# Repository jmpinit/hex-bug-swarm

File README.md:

# Hex Bug Swarm

[A blog post explaining what this is for](https://owentrueblood.com/hex-bug-swarm/)

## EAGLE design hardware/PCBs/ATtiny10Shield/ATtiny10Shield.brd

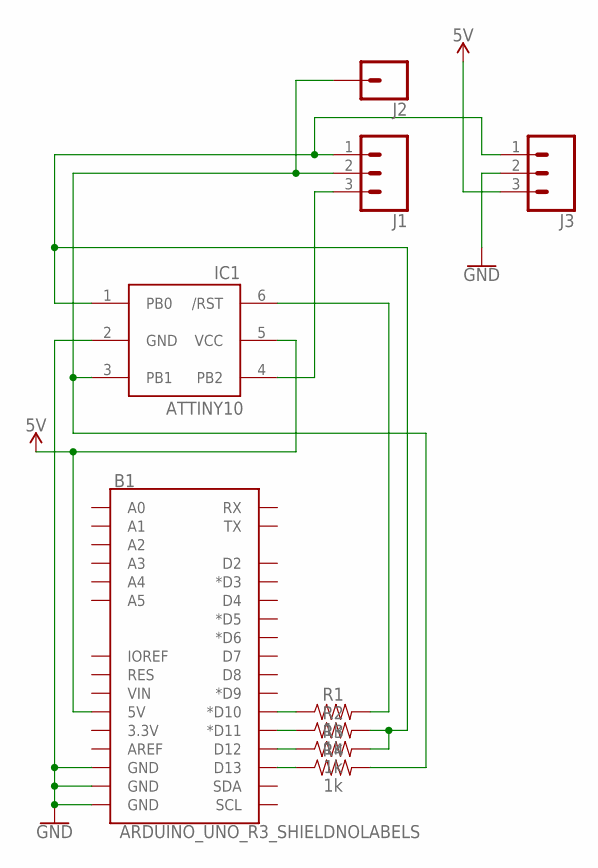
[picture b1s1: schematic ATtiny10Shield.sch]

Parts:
B1: ARDUINO_UNO_R3_SHIELDNOLABELS; UNO_R3_SHIELD_NOLABELS
IC1: ATTINY10; SOT23-6
J1, J3: CONN_03; 1X03
J2: CONN_01; 1X01
R1, R2, R3, R4: 1k; AXIAL-0.3

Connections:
5V: B1.5V, IC1.5 (VCC), J3.3
GND: B1.GND@0 (GND), B1.GND@1 (GND), B1.GND@2 (GND), IC1.2 (GND), J3.2
unnamed: B1.D10 (*D10), R1.P$1 (1)
unnamed: B1.D11 (*D11), R2.P$1 (1)
unnamed: B1.D12, R3.P$1 (1)
unnamed: B1.D13, R4.P$1 (1)
unnamed: IC1.1 (PB0), J1.1, J3.1, R2.P$2 (2), R3.P$2 (2)
unnamed: IC1.6 (/RST), R1.P$2 (2)
unnamed: IC1.3 (PB1), J1.2, J2.1, R4.P$2 (2)
unnamed: IC1.4 (PB2), J1.3

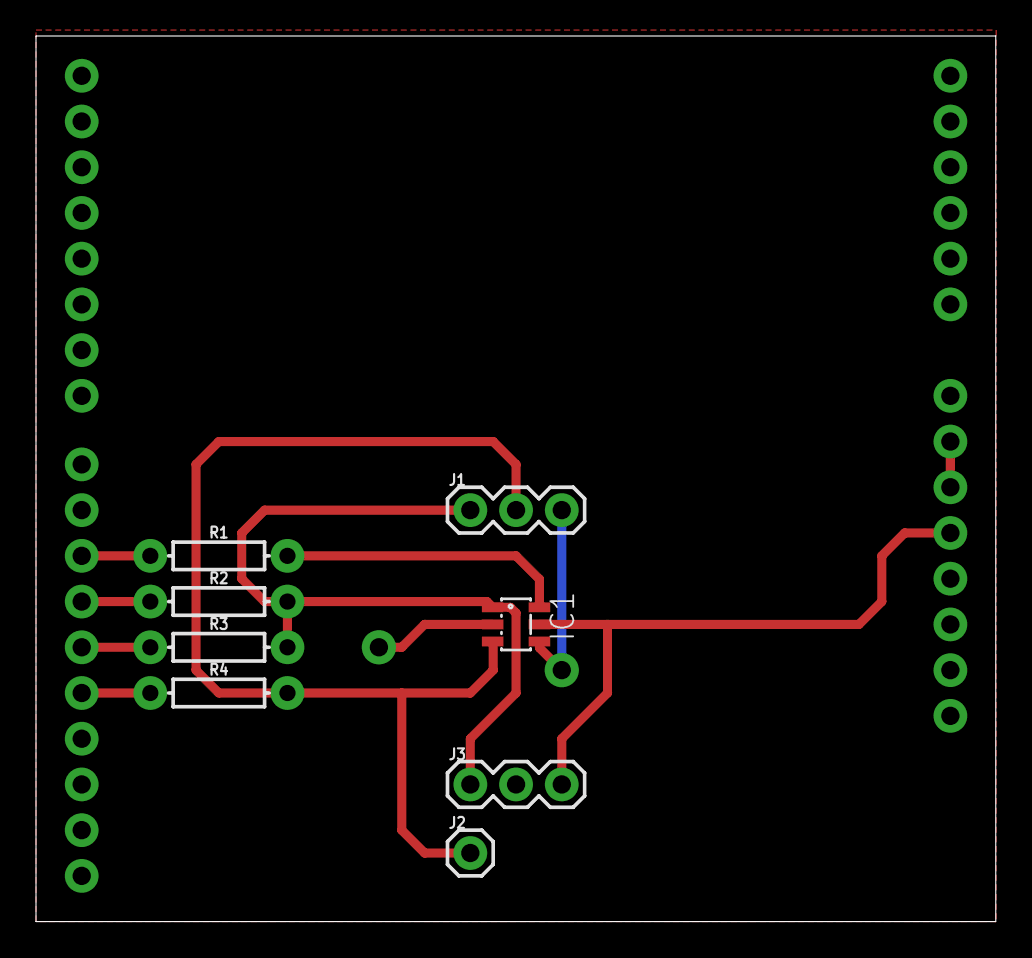
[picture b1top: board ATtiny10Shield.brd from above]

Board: 2 copper layers, 53.3 x 49.2 mm, 9 parts (0 on the bottom side), 10 nets.

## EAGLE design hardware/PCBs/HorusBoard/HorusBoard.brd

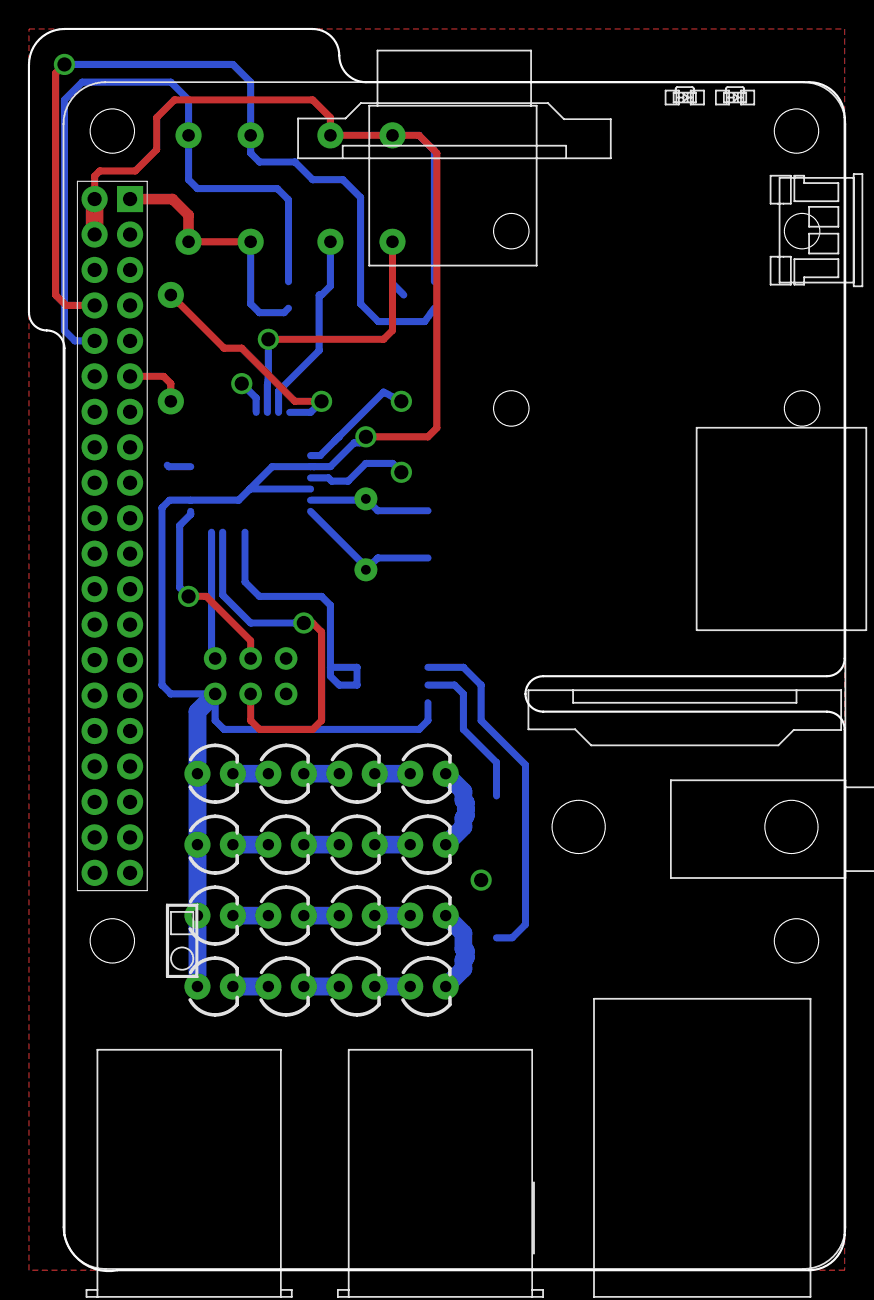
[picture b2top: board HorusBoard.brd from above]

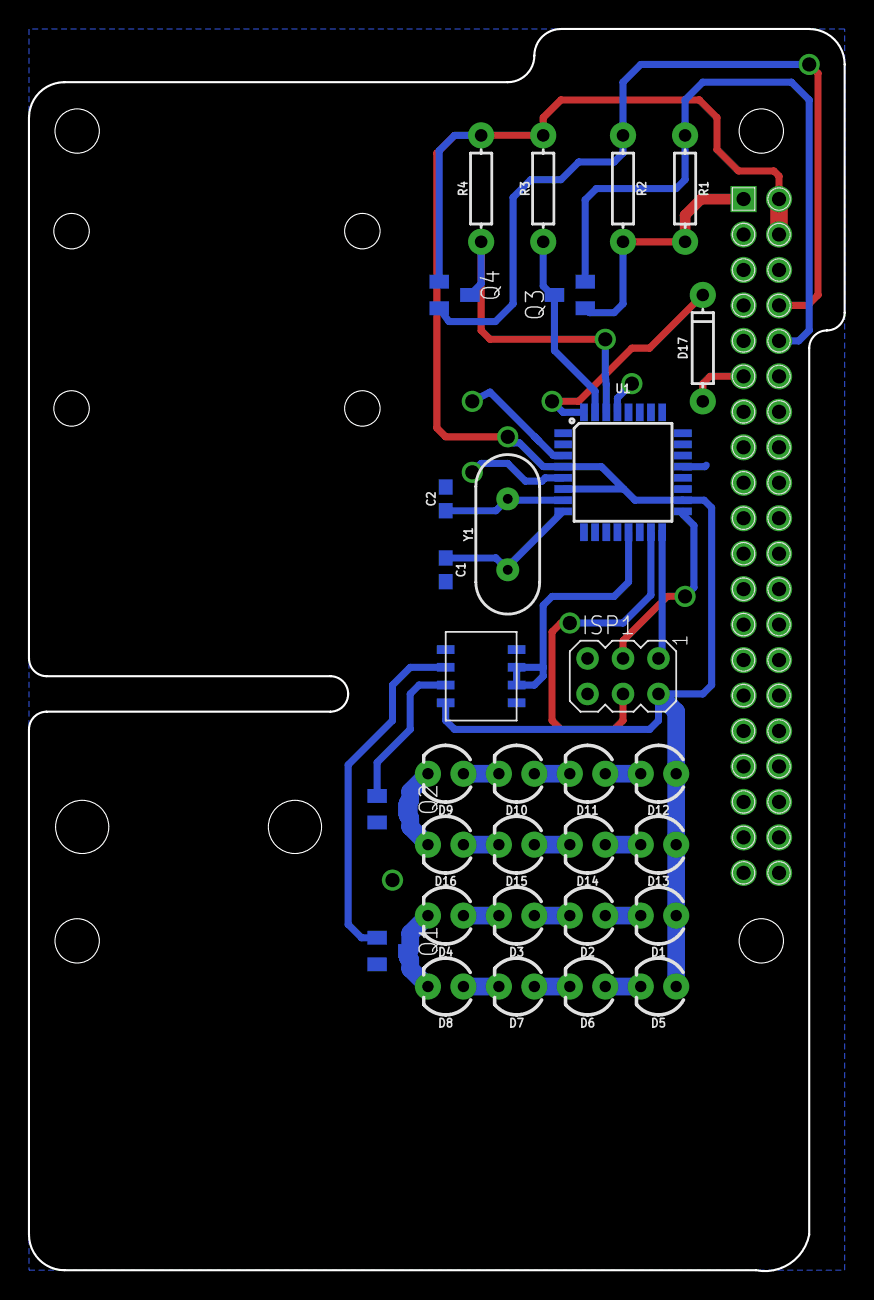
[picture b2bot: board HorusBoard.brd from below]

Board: 2 copper layers, 58.4 x 89.0 mm, 32 parts (31 on the bottom side), 32 nets.

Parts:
C1, C2: 22pF; 0603
D1, D2, D3, D4, D5, D6, D7, D8, D9, D10, D11, D12, D13, D14, D15, D16: LED_3MM
D17: 200mA/100V/1V; DIODE-1N4148
ISP1: AVRISP-6; AVRISP
Q1, Q2, Q3, Q4: SOT23
R1, R2, R3, R4: 1k; AXIAL-0.3
U1: ATMEGA328P_TQFP; TQFP32-08
U$1: TC4427; 8-SOIC
U$2: RASPBERRY_PI_3
Y1: 16MHz; HC49US

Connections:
3.3V: Q3.1, R1.P$2, R2.P$2, U$2.1
5V: D1.A, D5.A, D12.A, D13.A, ISP1.2, Q4.1, R3.P$2, R4.P$2, U1.4, U1.6, U1.18, U$1.P$8, U$2.2, U$2.4
GND: C1.2, C2.2, ISP1.6, Q1.2, Q2.2, U1.3, U1.5, U1.21, U$1.P$1, U$2.6, U$2.9, U$2.14, U$2.20, U$2.25, U$2.30, U$2.34, U$2.39
LIGHT: U1.13, U$1.P$2, U$1.P$3
MISO: ISP1.1, U1.16
MOSI: ISP1.4, U1.15
unnamed: D4.K, D8.K, Q1.3
unnamed: D9.K, D16.K, Q2.3
unnamed: Q1.1, U$1.P$6
unnamed: D17.A, U$2.11
unnamed: Q2.1, U$1.P$7
unnamed: C2.1, U1.7, Y1.2
unnamed: C1.1, U1.8, Y1.1
unnamed: D1.K, D2.A
unnamed: D2.K, D3.A
unnamed: D3.K, D4.A
unnamed: D7.K, D8.A
unnamed: D9.A, D10.K
unnamed: D6.K, D7.A
unnamed: D10.A, D11.K
unnamed: D14.K, D15.A
unnamed: D15.K, D16.A
unnamed: D11.A, D12.K
unnamed: D5.K, D6.A
unnamed: D13.K, D14.A
unnamed: D17.C, U1.32
RESET: ISP1.5, U1.29
RX_3.3V: Q3.2, R1.P$1, U$2.10
RX_5V: Q4.3, R4.P$1, U1.30
SCK: ISP1.3, U1.17
TX_3.3V: Q4.2, R2.P$1, U$2.8
TX_5V: Q3.3, R3.P$1, U1.31

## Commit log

2017-11-10 Move left side forward
2017-11-10 Milled this board 1st
    Needed to be hacksawed to clear the ports.
2017-11-10 All Hex Bug Fire Ant commands
2017-12-19 Send message over UART on INT0
2017-12-19 Measure pulse lengths
2017-12-19 Easy script to build code and test on an Arduino
2017-12-19 Reads IR packets
2017-12-19 Control hex bug via UART
2017-12-19 Only responds if message matches its ID
2017-12-20 Movement commands
2017-12-20 Act only as a serial to IR converter
2017-12-20 Ported to ATTiny10
2019-01-08 Dump for blog post
2019-01-08 Documentation

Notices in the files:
parts and their libraries:
SparkFun-Boards: Licensing: Creative Commons ShareAlike 4.0 International - https://creativecommons.org/licenses/by-sa/4.0
